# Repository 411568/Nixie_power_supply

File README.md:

<h2>🧐 Features</h2>

Nixie power supply is a dc/dc converter for powering nixie tubes from a 9V input. The power supply is based on the MC34063 converter IC.

<h2>💻 Resources</h2>

* [AndrewJKramer](http://andrewjkramer.net/usb-nixie-power-supply/)
* [HighVoltageForum](https://highvoltageforum.net/index.php?topic=66.0)
* [ArduinoForum](https://forum.arduino.cc/t/problem-with-mc34063-180v-power-supply-huge-voltage-drop-solved/299096)
* [gra-afch](https://gra-afch.com/how-it-works/power-supplies-for-nixie-clocks/)
* [electronics.stackexchange](https://electronics.stackexchange.com/questions/475084/mc34063-based-converter-accoustic-noise)

<h2>🛡️ License:</h2>

This project is licensed under the MIT License.

<h2> 🙋‍♂️Authors </h2>

- Krzysztof Sikora

<h2>💖Like my work?</h2>

If you have any questions about the project feel free to contact us via email: krzysieksikora717@gmail.com

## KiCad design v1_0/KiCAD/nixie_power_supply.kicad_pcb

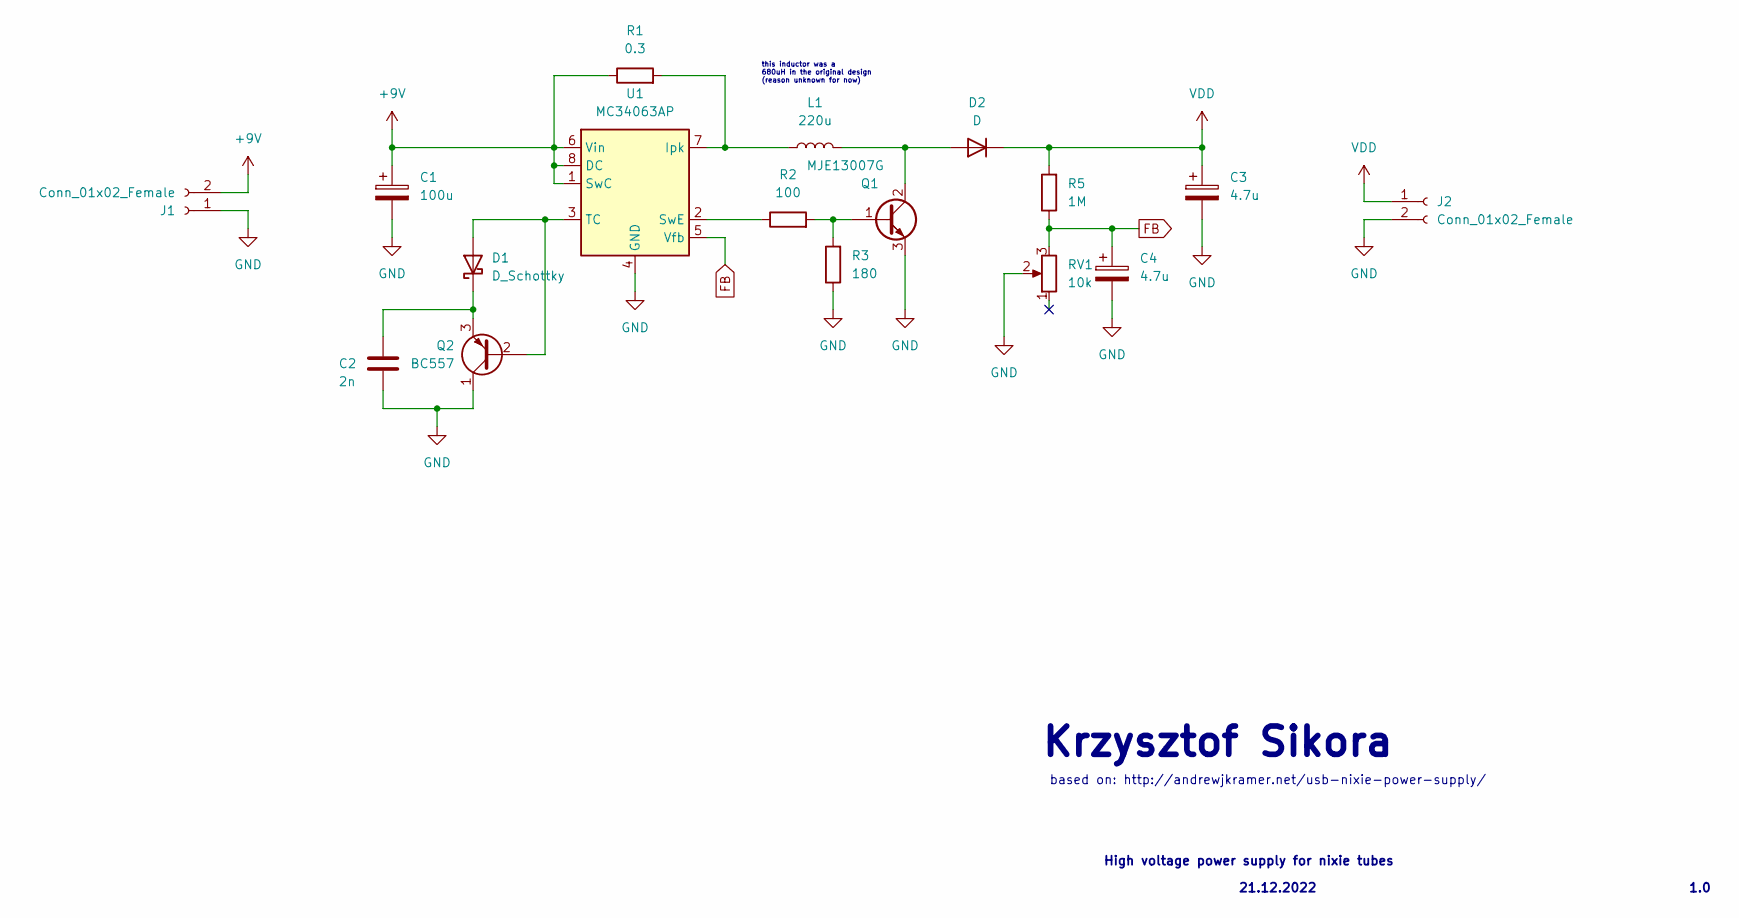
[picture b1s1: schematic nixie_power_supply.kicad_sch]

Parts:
C1: 100u; CP_Radial_D10.0mm_P3.80mm
C2: 2n; C_Disc_D3.4mm_W2.1mm_P2.50mm
C3, C4: 4.7u; CP_Radial_D6.3mm_P2.50mm
D1: D_Schottky; D_A-405_P10.16mm_Horizontal
D2: D; D_A-405_P10.16mm_Horizontal
J1, J2: Conn_01x02_Female; SolderWire-2sqmm_1x02_P7.8mm_D2mm_OD3.9mm
L1: 220u; L_Bourns_SDR1806
Q1: MJE13007G; TO-220-3_Vertical
Q2: BC557; TO-92_Inline
R1: 0.3; R_1206_3216Metric_Pad1.30x1.75mm_HandSolder
R2: 100; R_Axial_DIN0204_L3.6mm_D1.6mm_P5.08mm_Horizontal
R3: 180; R_Axial_DIN0204_L3.6mm_D1.6mm_P5.08mm_Horizontal
R5: 1M; R_Axial_DIN0204_L3.6mm_D1.6mm_P5.08mm_Horizontal
RV1: 10k; Potentiometer_ACP_CA6-H2,5_Horizontal
U1: MC34063AP; DIP-8_W7.62mm

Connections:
+9V: C1.1, J1.2, R1.1, U1.1 (SwC), U1.6 (Vin), U1.8 (DC)
FB: C4.1, R5.1, RV1.3, U1.5 (Vfb)
GND: C1.2, C2.2, C3.2, C4.2, J1.1, J2.2, Q1.3 (E), Q2.1 (C), R3.1, RV1.2, U1.4 (GND)
unnamed: C2.1, D1.1 (K), Q2.3 (E)
unnamed: D1.2 (A), Q2.2 (B), U1.3 (TC)
unnamed: D2.2 (A), L1.2, Q1.2 (C)
unnamed: L1.1, R1.2, U1.7 (Ipk)
unnamed: Q1.1 (B), R2.2, R3.2
unnamed: R2.1, U1.2 (SwE)
VDD: C3.1, D2.1 (K), J2.1, R5.2

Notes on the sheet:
High voltage power supply for nixie tubes
based on: http://andrewjkramer.net/usb-nixie-power-supply/
1.0
21.12.2022
this inductor was a 680uH in the original design (reason unknown for now)
Krzysztof Sikora

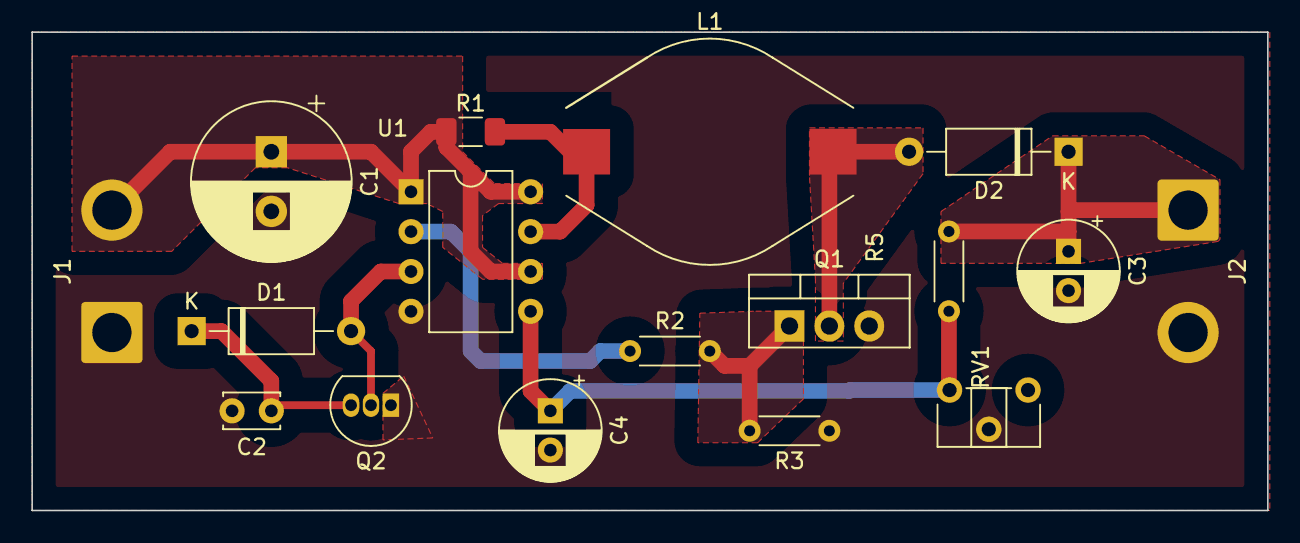
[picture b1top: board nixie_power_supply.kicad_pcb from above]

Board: 2 copper layers, 78.7 x 30.5 mm, 17 parts (0 on the bottom side), 10 nets.

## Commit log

2023-01-03 v1_0 first commit
2023-01-03 add README
2025-01-30 Create LICENSE
